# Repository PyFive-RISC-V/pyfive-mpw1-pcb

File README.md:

# pyfive-mpw1-pcb
Breakout carrier for the MPW1 PyFive chip

PyFive specific pins
* mprj_io[11] = usb_dn
* mprj_io[12] = usb_dp
* mprj_io[13] = usb_pu
* mprj_io[14] = usb_sof
* mprj_io[15] = midi_tx
* mprj_io[16] = midi_rx
* mprj_io[17] = pcm_audio_1
* mprj_io[18] = pcm_audio_2
* mprj_io[19] = video_clk
* mprj_io[20] = video_de
* mprj_io[21] = video_hsync
* mprj_io[22] = video_vsync
* mprj_io[23] = video_r
* mprj_io[24] = video_g
* mprj_io[25] = video_b
* mprj_io[26] = video_i

Features
* Input current jumpers
* External clock input header
* 2.54" programming headers
* PCM => RC filter => op-amp => headphone jack
* Header for video output to DVI PMOD
* Buttons

Based on the [caravel_carrier](https://github.com/samlittlewood/caravel_carrier) design by Sam Littlewood.

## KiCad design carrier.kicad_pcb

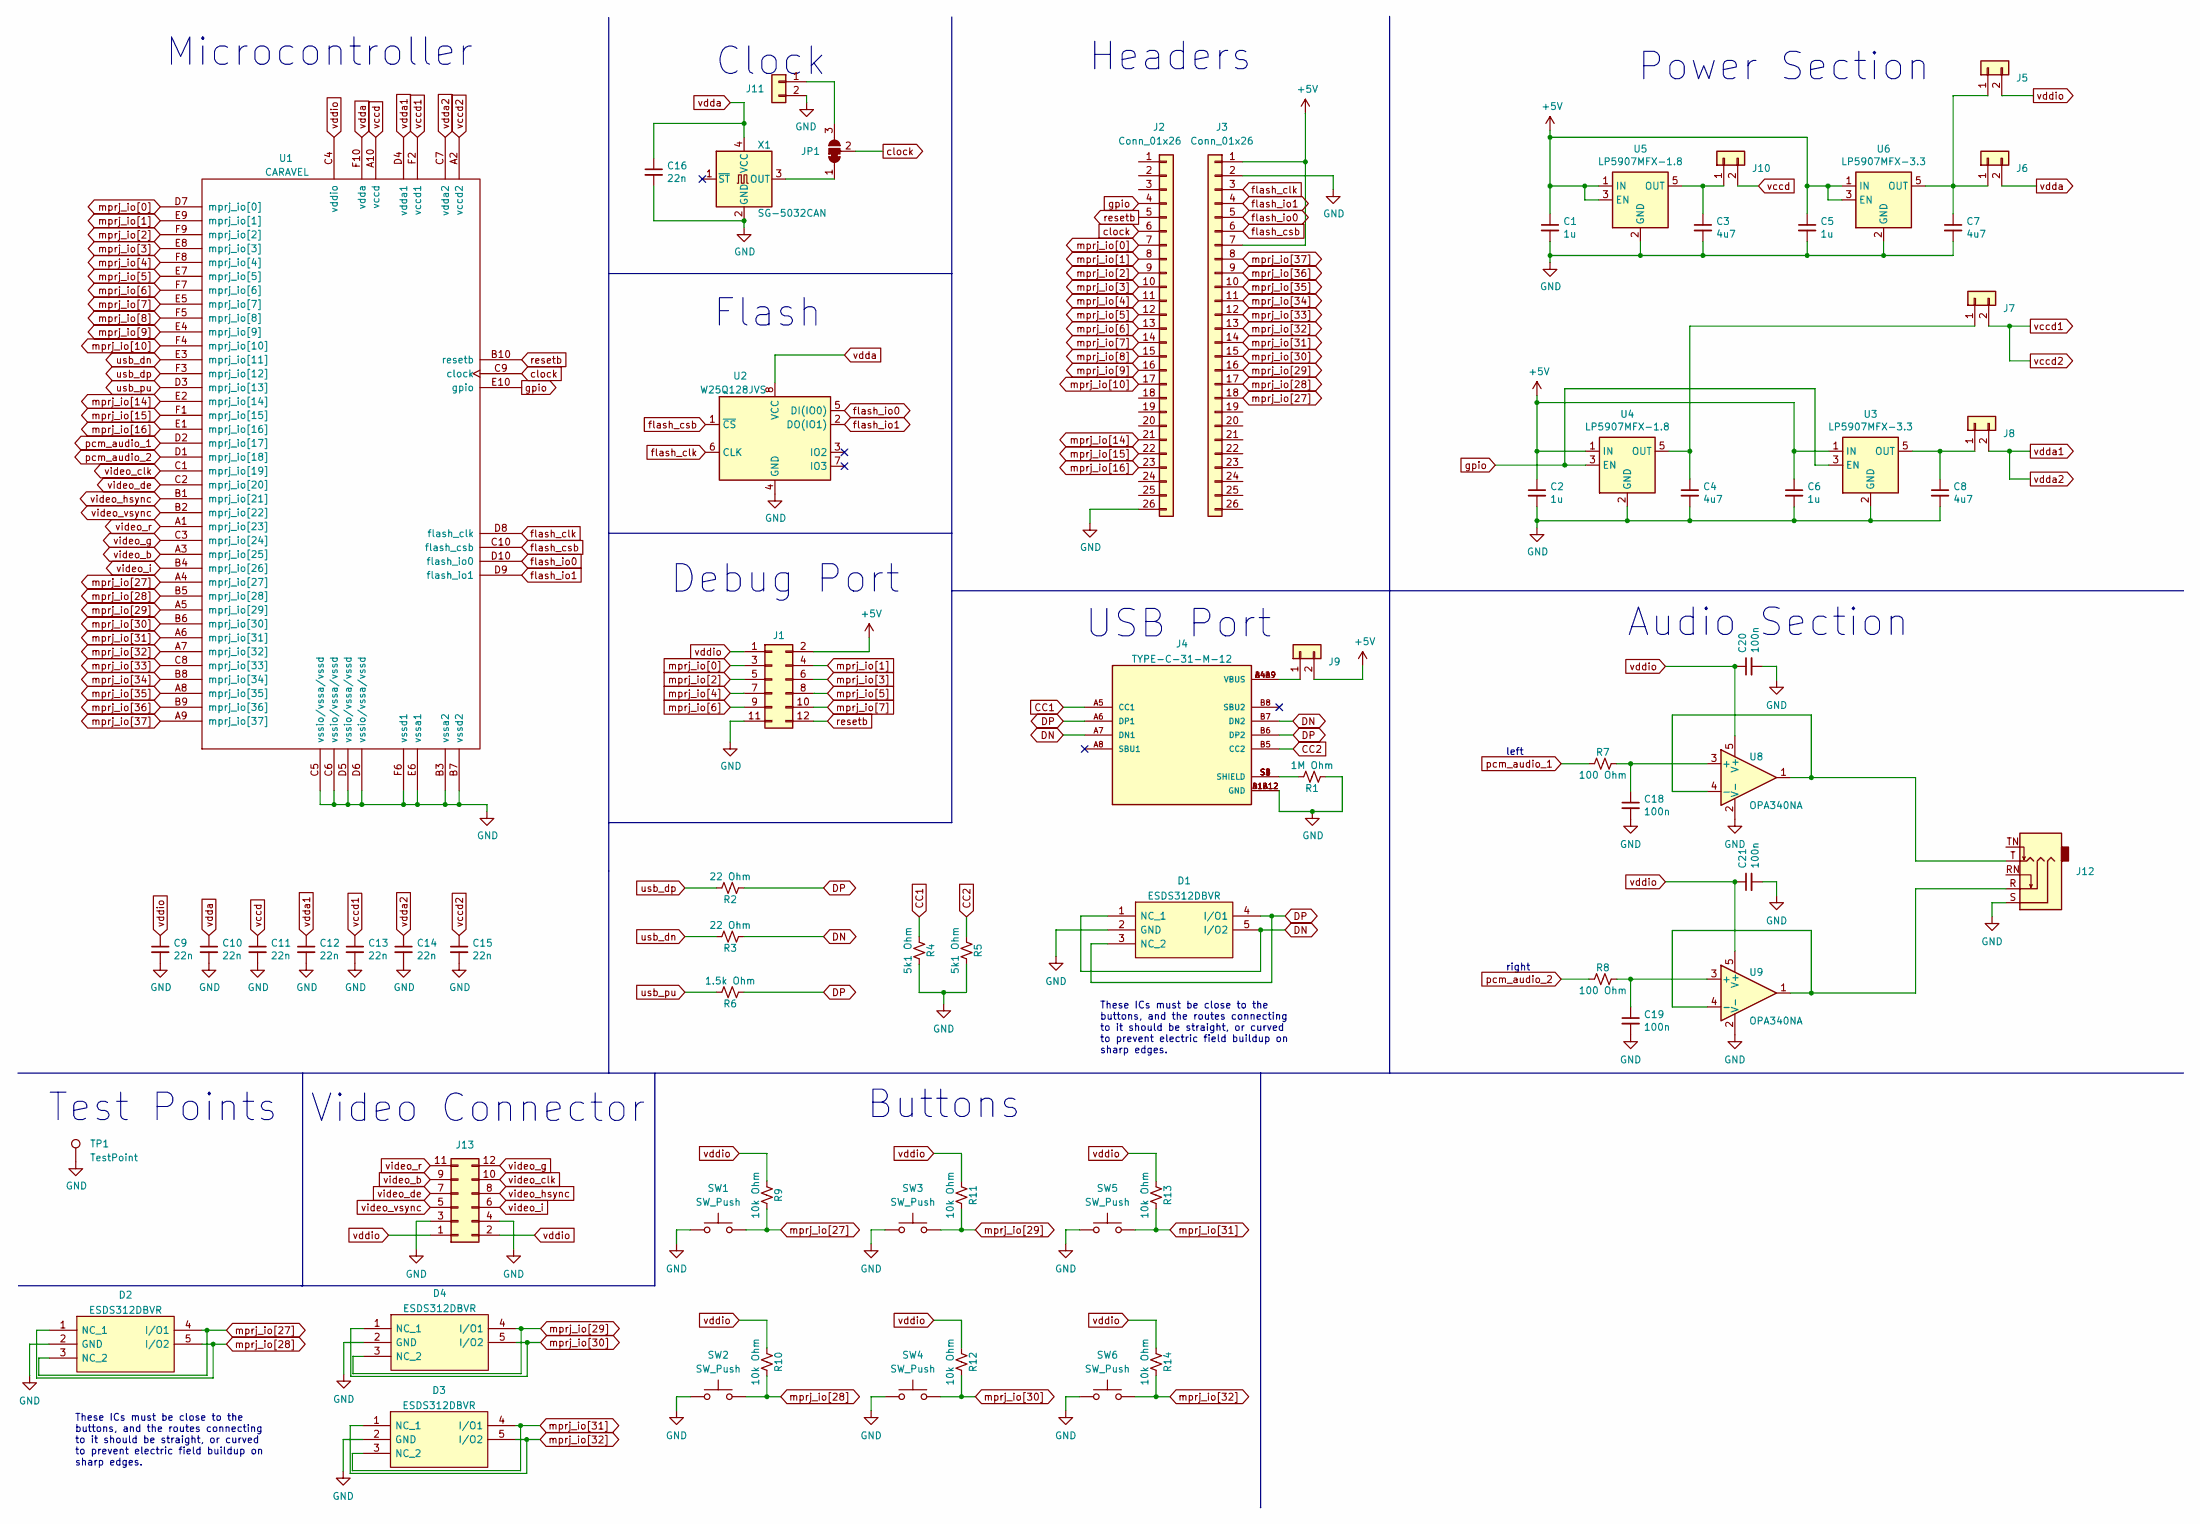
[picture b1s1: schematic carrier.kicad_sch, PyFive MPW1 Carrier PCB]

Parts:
C1, C2, C5, C6: 1u; C_0603_1608Metric
C3, C4, C7, C8: 4u7; C_0603_1608Metric
C9, C10, C11, C12, C13, C14, C15, C16: 22n; C_0402_1005Metric
C18, C19, C20, C21: 100n; C_0402_1005Metric
D1, D2, D3, D4: ESDS312DBVR; SOT-23-5; Manufacturer_Part_Number ESDS312DBVR; Mouser Part Number 595-ESDS312DBVR
J1: Conn_02x06_Odd_Even; PinHeader_2x06_P2.54mm_Vertical
J2, J3: Conn_01x26; PinHeader_1x26_P2.54mm_Vertical
J4: TYPE-C-31-M-12; HRO_TYPE-C-31-M-12; PARTREV A
J5, J6, J7, J8, J9, J10, J11: Conn_01x02; PinHeader_1x02_P2.54mm_Vertical
J12: AudioJack3_SwitchTR; Jack_3.5mm_CUI_SJ1-3535NG_Horizontal_CircularHoles
J13: Conn_02x06_Odd_Even; PinSocket_2x06_P2.54mm_Horizontal
JP1: SolderJumper_3_Bridged12; SolderJumper-3_P1.3mm_Bridged12_Pad1.0x1.5mm
R1: 1M Ohm; R_0402_1005Metric
R2, R3: 22 Ohm; R_0402_1005Metric
R4, R5: 5k1 Ohm; R_0402_1005Metric
R6: 1.5k Ohm; R_0402_1005Metric
R7, R8: 100 Ohm; R_0402_1005Metric
R9, R10, R11, R12, R13, R14: 10k Ohm; R_0402_1005Metric
SW1, SW2, SW3, SW4, SW5, SW6: SW_Push; SW_Push_1P1T_NO_CK_KMR2
TP1: TestPoint; TestPoint_Keystone_5000-5004_Miniature
U1: CARAVEL; WLCSP-60_P0.5mm
U2: W25Q128JVS; SOIC-8_5.23x5.23mm_P1.27mm
U3, U6: LP5907MFX-3.3; SOT-23-5
U4, U5: LP5907MFX-1.8; SOT-23-5
U8, U9: OPA340NA; SOT-23-5
X1: SG-5032CAN; Oscillator_SMD_SeikoEpson_SG8002LB-4Pin_5.0x3.2mm

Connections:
+5V: C1.1, C2.1, C5.1, C6.1, J1.2, J3.1, J3.7, J9.2, U3.1 (IN), U4.1 (IN), U5.1 (IN), U5.3 (EN), U6.1 (IN), U6.3 (EN)
CC1: J4.A5 (CC1), R4.2
CC2: J4.B5 (CC2), R5.2
DN: D1.1 (NC_1), D1.5 (I/O2), J4.A7 (DN1), J4.B7 (DN2), R3.2
DP: D1.3 (NC_2), D1.4 (I/O1), J4.A6 (DP1), J4.B6 (DP2), R2.2, R6.2
GND: C1.2, C2.2, C3.2, C4.2, C5.2, C6.2, C7.2, C8.2, C9.2, C10.2, C11.2, C12.2, C13.2, C14.2, C15.2, C16.2, C18.2, C19.2, C20.2, C21.2, D1.2 (GND), D2.2 (GND), D3.2 (GND), D4.2 (GND), J1.11, J2.26, J3.2, J4.A1B12 (GND), J4.B1A12 (GND), J11.2, J12.S, J13.3, J13.4, R1.2, R4.1, R5.1, SW1.1, SW2.1, SW3.1, SW4.1, SW5.1, SW6.1, TP1.1, U1.B3 (vssa2), U1.B7 (vssd2), U1.C5 (vssio/vssa/vssd), U1.C6 (vssio/vssa/vssd), U1.D5 (vssio/vssa/vssd), U1.D6 (vssio/vssa/vssd), U1.E6 (vssa1), U1.F6 (vssd1), U2.4 (GND), U3.2 (GND), U4.2 (GND), U5.2 (GND), U6.2 (GND), U8.2 (V-), U9.2 (V-), X1.2 (GND)
unnamed: C3.1, J10.1, U5.5 (OUT)
unnamed: C4.1, J7.1, U4.5 (OUT)
unnamed: C7.1, J5.1, J6.1, U6.5 (OUT)
unnamed: C8.1, J8.1, U3.5 (OUT)
unnamed: C18.1, R7.1, U8.3 (+)
unnamed: C19.1, R8.1, U9.3 (+)
unnamed: J4.A4B9 (VBUS), J4.B4A9 (VBUS), J9.1
unnamed: J4.S1 (SHIELD), J4.S2 (SHIELD), J4.S3 (SHIELD), J4.S4 (SHIELD), R1.1
unnamed: J11.1, JP1.3 (B)
unnamed: J12.R, U9.1, U9.4 (-)
unnamed: J12.T, U8.1, U8.4 (-)
unnamed: JP1.1 (A), X1.3 (OUT)
clock: J2.6, JP1.2 (C), U1.C9 (clock)
flash_clk: J3.3, U1.D8 (flash_clk), U2.6 (CLK)
flash_csb: J3.6, U1.C10 (flash_csb), U2.1 (~CS)
flash_io0: J3.5, U1.D10 (flash_io0), U2.5 (DI(IO0))
flash_io1: J3.4, U1.D9 (flash_io1), U2.2 (DO(IO1))
gpio: J2.4, U1.E10 (gpio), U3.3 (EN), U4.3 (EN)
mprj_io[0]: J1.3, J2.7, U1.D7 (mprj_io[0])
mprj_io[1]: J1.4, J2.8, U1.E9 (mprj_io[1])
mprj_io[2]: J1.5, J2.9, U1.F9 (mprj_io[2])
mprj_io[3]: J1.6, J2.10, U1.E8 (mprj_io[3])
mprj_io[4]: J1.7, J2.11, U1.F8 (mprj_io[4])
mprj_io[5]: J1.8, J2.12, U1.E7 (mprj_io[5])
mprj_io[6]: J1.9, J2.13, U1.F7 (mprj_io[6])
mprj_io[7]: J1.10, J2.14, U1.E5 (mprj_io[7])
mprj_io[8]: J2.15, U1.F5 (mprj_io[8])
mprj_io[9]: J2.16, U1.E4 (mprj_io[9])
mprj_io[10]: J2.17, U1.F4 (mprj_io[10])
mprj_io[14]: J2.21, U1.E2 (mprj_io[14])
mprj_io[15]: J2.22, U1.F1 (mprj_io[15])
mprj_io[16]: J2.23, U1.E1 (mprj_io[16])
mprj_io[27]: D2.3 (NC_2), D2.4 (I/O1), J3.18, R9.1, SW1.2, U1.A4 (mprj_io[27])
mprj_io[28]: D2.1 (NC_1), D2.5 (I/O2), J3.17, R10.1, SW2.2, U1.B5 (mprj_io[28])
mprj_io[29]: D4.3 (NC_2), D4.4 (I/O1), J3.16, R11.1, SW3.2, U1.A5 (mprj_io[29])
mprj_io[30]: D4.1 (NC_1), D4.5 (I/O2), J3.15, R12.1, SW4.2, U1.B6 (mprj_io[30])
mprj_io[31]: D3.3 (NC_2), D3.4 (I/O1), J3.14, R13.1, SW5.2, U1.A6 (mprj_io[31])
mprj_io[32]: D3.1 (NC_1), D3.5 (I/O2), J3.13, R14.1, SW6.2, U1.A7 (mprj_io[32])
mprj_io[33]: J3.12, U1.C8 (mprj_io[33])
mprj_io[34]: J3.11, U1.B8 (mprj_io[34])
mprj_io[35]: J3.10, U1.A8 (mprj_io[35])
mprj_io[36]: J3.9, U1.B9 (mprj_io[36])
mprj_io[37]: J3.8, U1.A9 (mprj_io[37])
pcm_audio_1: R7.2, U1.D2 (mprj_io[17])
pcm_audio_2: R8.2, U1.D1 (mprj_io[18])
resetb: J1.12, J2.5, U1.B10 (resetb)
usb_dn: R3.1, U1.E3 (mprj_io[11])
usb_dp: R2.1, U1.F3 (mprj_io[12])
usb_pu: R6.1, U1.D3 (mprj_io[13])
vccd: C11.1, J10.2, U1.A10 (vccd)
vccd1: C13.1, C15.1, J7.2, U1.A2 (vccd2), U1.F2 (vccd1)
vdda: C10.1, C16.1, J6.2, U1.F10 (vdda), U2.8 (VCC), X1.4 (VCC)
vdda1: C12.1, C14.1, J8.2, U1.C7 (vdda2), U1.D4 (vdda1)
vddio: C9.1, C20.1, C21.1, J1.1, J5.2, J13.1, J13.2, R9.2, R10.2, R11.2, R12.2, R13.2, R14.2, U1.C4 (vddio), U8.5 (V+), U9.5 (V+)
video_b: J13.9, U1.A3 (mprj_io[25])
video_clk: J13.10, U1.C1 (mprj_io[19])
video_de: J13.7, U1.C2 (mprj_io[20])
video_g: J13.12, U1.C3 (mprj_io[24])
video_hsync: J13.8, U1.B1 (mprj_io[21])
video_i: J13.6, U1.B4 (mprj_io[26])
video_r: J13.11, U1.A1 (mprj_io[23])
video_vsync: J13.5, U1.B2 (mprj_io[22])

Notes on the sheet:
Test Points
These ICs must be close to the buttons, and the routes connecting to it should be straight, or curved to prevent electric field buildup on sharp edges.
Microcontroller
Video Connector
Debug Port
Flash
Clock
Buttons
USB Port
Headers
left
right
Audio Section
Power Section

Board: 4 copper layers, 68 parts (0 on the bottom side), 68 nets, no tracks yet.

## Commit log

2021-09-10 Update README.md
    Break down the video lines to components in README
2021-09-10 Manually fork carvel_carrier design
    Pulls in the caravel_carrier design from Sam Littlewood (mentioned in schematic header)
    Brings design to KiCad 5.99 format.
    Removes random silkscreen.
2021-09-10 Update README.md
    Make sure credit is given to the original author of caravel_carrier.
2021-09-10 Create LICENSE
    Pull license in from caravel_carrier design to be legit.
2021-09-25 Cleanup schematics by dividing it into relevant sections
2021-09-25 Added schematics for USB Section
2021-09-25 Switch to 2.54mm header for programming
    Also imports changes from schematic to PCB.
2021-09-25 Update caravel ASIC footprint
    It was mirrored about the Y-axis.
    Thanks to Tim Edwards and Matt Venn for flagging this issue.
2021-09-25 Add current measurement jumpers
    Removes solder bridges and adds jumpers for each power rail to measure current.
2021-09-25 Add provision for external clk on pin header
    Uses a solder jumper to select oscillator by default.
2021-09-26 Add audio circuitry
    Adds headphone output for the PCM audio output
2021-09-26 Add GND hook test point
    Might want to add more test points for various things.
2021-09-26 Add video connector
    May want to use PMOD specific connector numbering to avoid confusion.
2021-09-26 Add some buttons
    May want to consider adding ESD clamps to buttons.
2021-09-26 schematics: Replaced TPD2E001DRSR with ESDS312DBVR
    ESDS312DBVR has a better footprint which makes routing around it easier.
    Also, it is much cheaper than the earlier chip used.
    Fixes #13
2021-09-26 schematics: Changed the colour of ESDS312DBVR to match other footprints
2021-09-26 schematics: Cleanup schematics
    * Divide the subcircuits using grid
    * Annotate symbol name to ESDS312DBVR
2021-09-26 schematics: Added ESD Protection for buttons
    Add ESDS312DBVR chip to the input GPIOs connected to the buttons.
2021-09-26 Switch KiCAD standard SOT-23-5 footprint
    No need to reinvent the wheel.
2021-09-29 schematics: Add subcircuit for RGB LED
    * Uses LRTBGVSRU4V2JWA6BBD8S2U27Z20S RGB Led, with common cathode config
